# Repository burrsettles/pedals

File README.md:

# BULLFINCH EFFECTS

This repo contains work-in-progress circuit designs for DIY guitar effect pedals.

I write songs and play guitar for [delicious pastries](https://soundcloud.com/deliciouspastries/albums); as our sound has became more effects-driven, I became interested in the underlying technology of  analog effects. So I built a few boutique pedals/clones from stompbox kits and PCBs designed by others. I'm now at a point where I want to experiment with my own circuit modifications, designs, and layouts. This is a playground for that.

### Verified designs with build docs to date:

- [CYCLOPS](designs/cyclops_fuzz/) (mufflike fuzz)
- [GAIUS](designs/gaius_ringer/) (octaver / ring modulator)
- [JANUS](designs/janus_overdrive) (overdrive + distortion)
- [SIREN](designs/siren_chorus) (PT2399 chorus)

Subfolders contain files for [EAGLE](http://www.cadsoftusa.com/) schematics and two-sided circuit boards (e.g., for an [OSH Park](https://oshpark.com/) order), and maybe some documentation. The `bffx-lbr` directory contains the EAGLE library I'm using. I am not making any one-sided layouts, since I don't want to etch my own PCBs (for now). At this point, no designs are verified or even finalized. As time goes on, I will actually build and test these, and documentation will be more complete! :)

I'm naming the pedals after various mythological characters or elements.

© 2016 Burr Settles ([LICENSE](LICENSE.md))

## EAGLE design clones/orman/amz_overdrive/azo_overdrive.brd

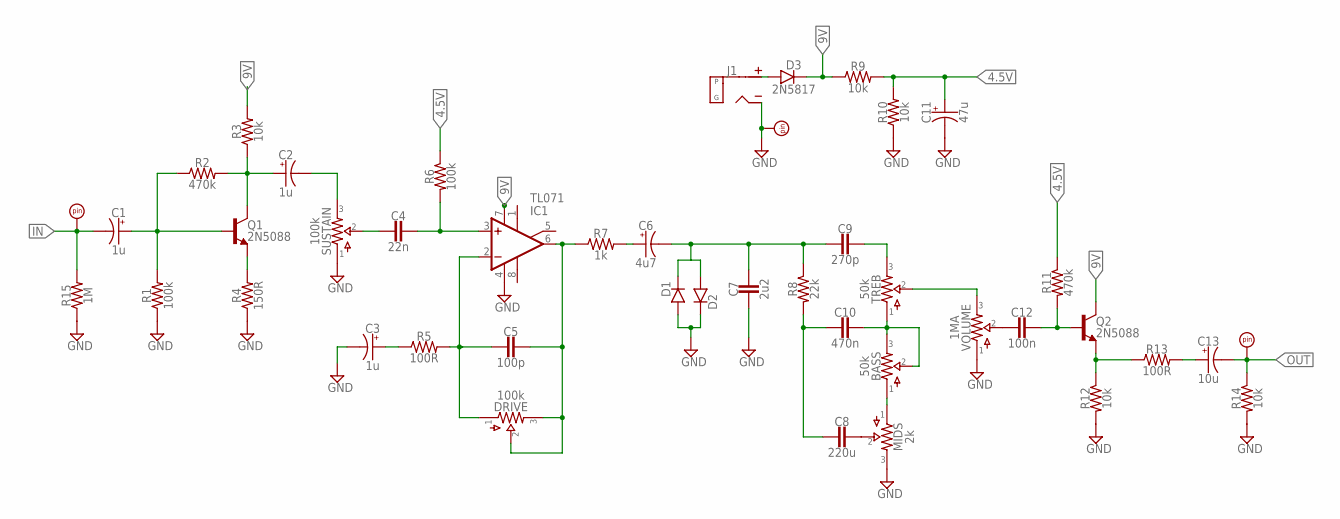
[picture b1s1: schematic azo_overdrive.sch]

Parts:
BASS: 50k; 16MM
C1, C2, C3: 1u; 050_020_1
C4: 22n; 050X030_025_2
C5: 100p; 050X030_025_2
C6: 4u7; 050_020_1
C7: 2u2; 050X030_025_2
C8: 220u; 050X030_025_2
C9: 270p; 050X030_025_2
C10: 470n; 050X030_025_2
C11: 47u; 050_020_1
C12: 100n; 050X030_025_2
C13: 10u; 050_020_1
D1, D2: DO35.2; DO35-2
D3: 2N5817; DO41-3
DRIVE: 100k; 16MM
GND: PADSQR; SQUARE
IC1: TL071; DIL08
IN: PADSQR; SQUARE
J1: DC_MONO; DC
MIDS: 2k; 16MM
OUT: PADSQR; SQUARE
Q1, Q2: 2N5088; TO92-
R1, R6: 100k; R0207/3
R2, R11: 470k; R0207/3
R3, R9, R10, R12, R14: 10k; R0207/3
R4: 150R; R0207/3
R5, R13: 100R; R0207/3
R7: 1k; R0207/3
R8: 22k; R0207/3
R15: 1M; R0207/3
SUSTAIN: 100k; 2262_TRIM
TREB: 50k; 16MM
VOLUME: 1MA; 16MM

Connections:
4.5V: C11.+, R6.1, R9.2, R10.2, R11.1
9V: D3.C, IC1.7 (V+), Q2.1 (C), R3.2, R9.1
GND: C3.-, C7.2, C11.-, D1.A, D2.C, GND.1, IC1.4 (V-), J1.S (SLEEVE), MIDS.3, R1.1, R4.1, R10.1, R12.2, R14.2, R15.1, SUSTAIN.1, VOLUME.1
IN: C1.-, IN.1, R15.2
unnamed: C1.+, Q1.2 (B), R1.2, R2.1
unnamed: C4.1, IC1.3 (+IN), R6.2
unnamed: C2.+, Q1.1 (C), R2.2, R3.1
unnamed: Q1.3 (E), R4.2
unnamed: C2.-, SUSTAIN.3
unnamed: D3.A, J1.T (TIP)
unnamed: C5.2, DRIVE.1, IC1.2 (-IN), R5.2
unnamed: C3.+, R5.1
unnamed: C4.2, SUSTAIN.2
unnamed: C6.-, C7.1, C9.2, D1.C, D2.A, R8.1
unnamed: C5.1, DRIVE.2, DRIVE.3, IC1.6 (OUT), R7.1
unnamed: C8.1, MIDS.2
unnamed: C6.+, R7.2
unnamed: C9.1, TREB.3
unnamed: C8.2, C10.2, R8.2
unnamed: BASS.2, BASS.3, C10.1, TREB.1
unnamed: BASS.1, MIDS.1
unnamed: C12.1, Q2.2 (B), R11.2
unnamed: TREB.2, VOLUME.3
unnamed: C12.2, VOLUME.2
unnamed: Q2.3 (E), R12.1, R13.1
unnamed: C13.+, R13.2
OUT: C13.-, OUT.1, R14.1

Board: 2 copper layers, 44 parts (1 on the bottom side), 27 nets, no tracks yet.

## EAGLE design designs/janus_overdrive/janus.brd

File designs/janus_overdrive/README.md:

# JANUS

**OVERDRIVE + DISTORTION**

© 2016 Burr Settles ([LICENSE](../../LICENSE.md))

### overview

JANUS is a versatile and open-ended dirt box; a mash-up of several classic 1970s distortions. The story begins with the [Dan Armstrong Blue Clipper](http://www.effectsdatabase.com/model/danarmstrong/blueclipper) (1972?), supposedly one of the first op-amp-based "smooth fuzz" effects. According to legend, someone from MXR picked one up at a NAMM convention and it was modified to create the [MXR Distortion+](https://en.wikipedia.org/wiki/MXR_Distortion_%2B) (1973). This was later was modded into the [DOD 250 Overdrive/Preamp](http://www.effectsdatabase.com/model/dod/first/250) (1976), cloned as the [Ross R-50](http://www.effectsdatabase.com/model/ross/r50) (1979), and even adapted into the [MXR MicroAmp](http://www.jimdunlop.com/product/m133-micro-amp) preamp/booster.

Since these are basically the same circuit with different component values, the same board lets you build a variant of any of them. JANUS uses a combination of values I settled on through experimentation, and adds a CLIP switch to toggle between different clipping diodes (or no diodes at all!). This makes JANUS a multi-faced, multi-purpose vintage distortion box packed into in a tiny package.

### notes

* The clipping diodes (D1-D4) are your choice. Experiment! In my build, I used a pair of 1N914s for D2-D3 (symmetrical), and a 3mm red LED coupled with a NOS germanium for D4-D5 (asymmetrical).
* If you use an on/off/on SPDT for the CLIP switch, the middle "off" position adds a third boost option. With the gain turned down and the volume up, it's a pretty transparent clean boost, but the the op-amp can be overdriven without the help of clipping diodes as you turn up the gain. But be prepared: _it is a lot louder_!
* If you don't want the CLIP switch options, you can either:
  1. jumper pin 2 to pin 1 and use D4-D5 (larger, 4-spaced diodes like germanium or Schottky), or
  2. jumper pin 2 to pin 3 and use D2-D3 (smaller, 3-spaced diodes like 1N914, 1N4148, or LEDs).
* If you want to omit the DRIVE control (as with the Blue Clipper), jumper pin 2 to 3. This is fixed at maximum gain.
* If you want to build a booster with one control (as with the MicroAmp), jumper pin 2 to 3 for the VOLUME pot, and use only the DRIVE control. (You may also want to add a 10k resistor from pin 1 to either 2 or 3 to be more faithful to that circuit). Be warned: I haven't verified this yet.

### bill of materials

I recommend building with the JANUS values, as these are the only ones I have verified.

Since I edited the circuit to my own liking and squeezed it all into a 1590a-sized board, components for some of the source circuits are omitted and you can't get a 100% faithful clone of _every_ circuit JANUS is based on. However, if you want to try a straight-up clone of one of the source effects, try the alternate component values below (column headings are links to source docs/schematics):

Part | **JANUS** | [Blue Clipper](http://tonepad.com/project.asp?id=49) | [MXR Dist+](http://tonepad.com/project.asp?id=2) | [DOD 250](https://sites.google.com/site/snmavronis/NeoClassicFX/741overdrive/research) | [Ross](http://www.home-wrecker.com/ross_distortion_tan.png) | [MicroAmp](http://www.electrosmash.com/mxr-microamp)
--- | --- | --- | --- | --- | --- | ---
C1 | **2n2** | - | 1n | - | 1n | -
C2 | **47u** | 100u | - | - | 10n | -
C3 | **10n** | 47n | 10n | 10n | 10n | 100n
C4 | **10u** | - | 1u | 10u | 1u | 1u
C5 | **47n** | 4u7 | 47n | 47n | 47n | 4u7
C6 | **4u7** | 4u7 | 1u | 4u7 | 1u | 15u
D1 | **1N5817** | - | - | - | - | -
D2-D3 | **your choice** | 1N914 (Si) | - | 1N4148 (Si) | - | -
D4-D5 | **your choice** | - | 1N270 (Ge) | - | 1N270 (Ge) | -
IC1 | **LM741** | LM741 | LM741 | LM741 | LM741 | LM741
R1 | **1M** | - | - | - | - | -
R2 | **22k** | 200k | 1M | 22k | 1M | 100k
R3 | **22k** | 240k | 1M | 22k | 1M | 100k
R4 | **4k7** | 150R | 4k7 | 4k7 | 4k7 | 2k7
R5 | **10k** | jumper | 10k | 10k | 10k | 10k
R6 | **470k** | jumper | 1M | 470k | 1M | 10M
R7 | **1M** | 150k | 1M | 1M | 1M | 56k
R8 | **10k** | 18k2 | 10k | 10k | 10k | 470R
CLIP | **SPDT** toggle | jumper 2-3 | jumper 2-1 | jumper 2-3 | jumper 2-1 | -
DRIVE | **500kC** | jumper 2-3 | 500kC | 500kC | 500kC | 500kC
VOLUME | **100kA** | 10kA | 50kA | 100kA | 50kB | jumper 2-3

Note: The Ross version supposedly used a 4558 dual op-amp. The JANUS is only laid out for single op-amp like the LM741.

### schematic

### layout

1.3" x 1.3" (1590a)

### build pics

12 June 2016

29 May 2017

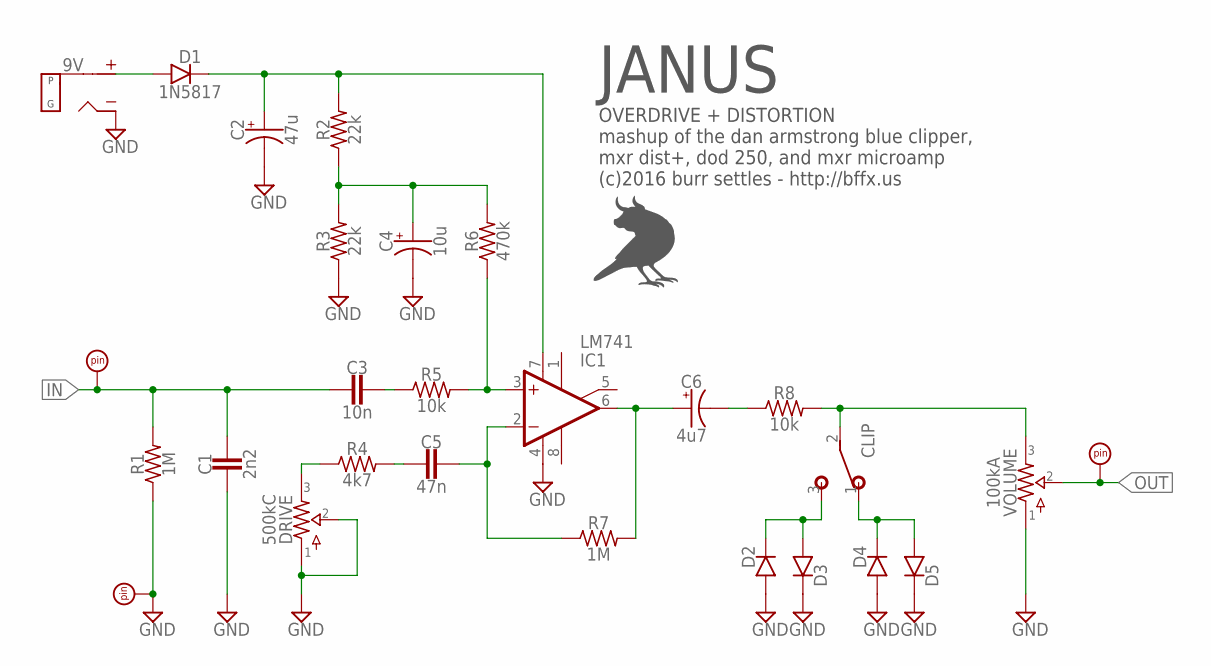
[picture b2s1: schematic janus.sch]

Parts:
9V: DC_MONO; DC
C1: 2n2; 050X030_025_2
C2: 47u; 050_020_1
C3: 10n; 050X030_025_2
C4: 10u; 050_020_1
C5: 47n; 050X030_025_2
C6: 4u7; 050_020_1
CLIP: SPDTPADS; SPDT
D1: 1N5817; DO41-3
D2, D3: DO35.2; DO35-2
D4, D5: DO35.3; DO35-3
DRIVE: 500kC; PADS_SMALL
GND: PADRND; ROUND
IC1: LM741; DIL08
IN: PADSQR; SQUARE
OUT: PADSQR; SQUARE
R1, R7: 1M; R0207/3
R2, R3: 22k; R0207/3
R4: 4k7; R0207/3
R5, R8: 10k; R0207/3
R6: 470k; R0207/3
VOLUME: 100kA; PADS_SMALL

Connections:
CLIP: CLIP.2, R8.2, VOLUME.3
GND: 9V.S (SLEEVE), C1.1, C2.-, C4.-, D2.A, D3.C, D4.A, D5.C, DRIVE.1, DRIVE.2, GND.1, IC1.4 (V-), R1.1, R3.1, VOLUME.1
IN: C1.2, C3.2, IN.1, R1.2
unnamed: C3.1, R5.1
unnamed: IC1.3 (+IN), R5.2, R6.1
unnamed: C5.1, IC1.2 (-IN), R7.1
unnamed: C5.2, R4.2
unnamed: C6.+, IC1.6 (OUT), R7.2
unnamed: C6.-, R8.1
unnamed: CLIP.3 (S), D2.C, D3.A
unnamed: C4.+, R2.1, R3.2, R6.2
unnamed: CLIP.1 (O), D4.C, D5.A
unnamed: DRIVE.3, R4.1
unnamed: 9V.T (TIP), D1.A
unnamed: C2.+, D1.C, IC1.7 (V+), R2.2
OUT: OUT.1, VOLUME.2

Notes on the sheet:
JANUS
OVERDRIVE + DISTORTION mashup of the dan armstrong blue clipper, mxr dist+, dod 250, and mxr microamp (c)2016 burr settles - http://bffx.us

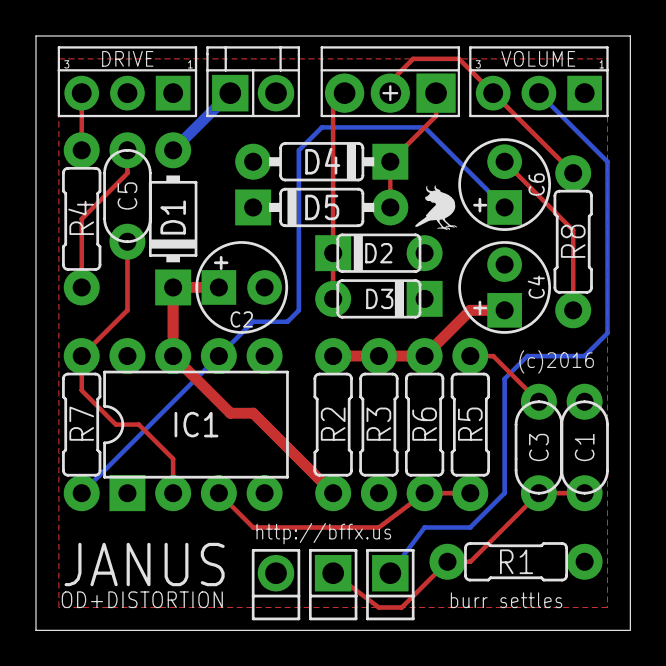
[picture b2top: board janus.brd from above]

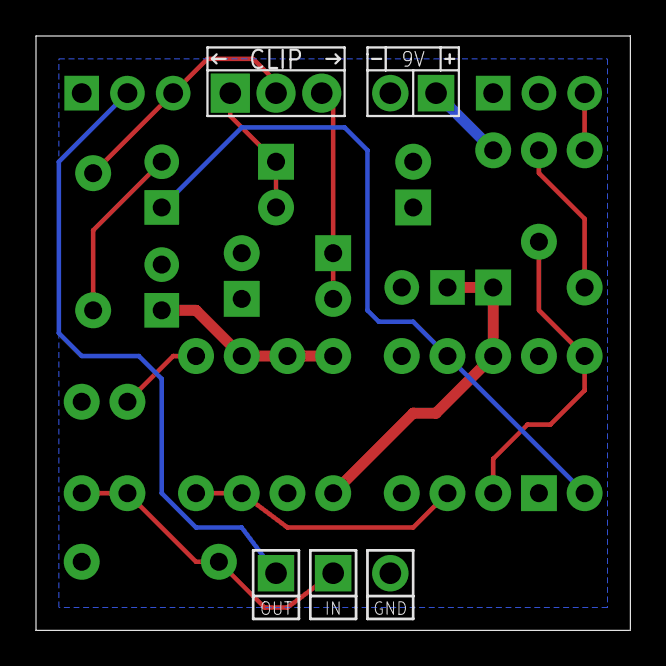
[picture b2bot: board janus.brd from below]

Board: 2 copper layers, 33.0 x 33.0 mm, 28 parts (2 on the bottom side), 16 nets.

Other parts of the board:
U$1: BF0100

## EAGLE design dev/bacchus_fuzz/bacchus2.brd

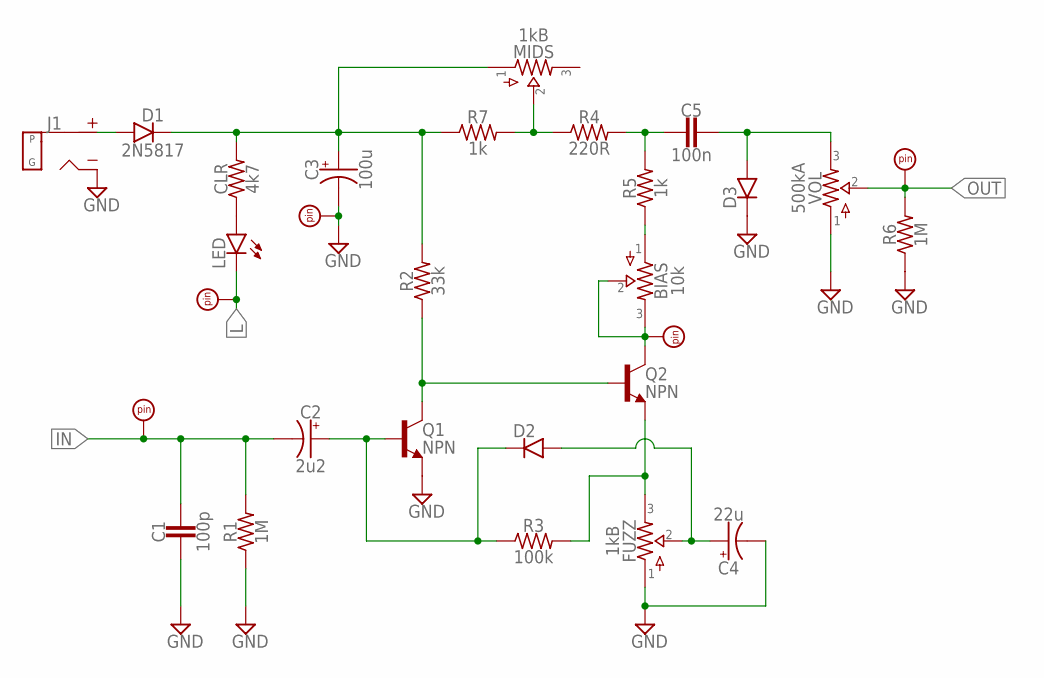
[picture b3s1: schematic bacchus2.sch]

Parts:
BIAS: 10k; 2262_TRIM
C1: 100p; 050X030_025_2
C2: 2u2; 050_020_1
C3: 100u; 050_020_1
C4: 22u; 050_020_1
C5: 100n; 050X030_025_2
CLR: 4k7; R0207/3
D1: 2N5817; DO41-3
D2, D3: DO35.2; DO35-2
FUZZ: 1kB; 9MM_W/MOUNTS
GND: PADRND; ROUND
IN: PADSQR; SQUARE
J1: DC_MONO; DC
L: PADRND; ROUND
LED: LEDB; 3MM_B
MIDS: 1kB; 9MM_W/MOUNTS
OUT: PADSQR; SQUARE
Q1, Q2: NPN; TO5
R1, R6: 1M; R0207/3
R2: 33k; R0207/3
R3: 100k; R0207/3
R4: 220R; R0207/3
R5, R7: 1k; R0207/3
TP: PADSQR; SQUARE
VOL: 500kA; 9MM_W/MOUNTS

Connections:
GND: C1.2, C3.-, C4.-, D3.C, FUZZ.P$1 (1), GND.1, J1.S (SLEEVE), Q1.1 (E), R1.1, R6.1, VOL.P$1 (1)
IN: C1.1, C2.-, IN.1, R1.2
L: L.1, LED.K (C)
unnamed: C5.1, D3.A, VOL.P$3 (3)
unnamed: C2.+, D2.C, Q1.2 (B), R3.1
unnamed: Q1.3 (C), Q2.2 (B), R2.1
unnamed: D1.A, J1.T (TIP)
unnamed: C3.+, CLR.2, D1.C, MIDS.P$1 (1), R2.2, R7.1
unnamed: MIDS.P$2 (2), R4.1, R7.2
unnamed: CLR.1, LED.A
unnamed: C5.2, R4.2, R5.2
unnamed: BIAS.1, R5.1
unnamed: BIAS.2, BIAS.3, Q2.3 (C), TP.1
unnamed: FUZZ.P$3 (3), Q2.1 (E), R3.2
unnamed: C4.+, D2.A, FUZZ.P$2 (2)
OUT: OUT.1, R6.2, VOL.P$2 (2)

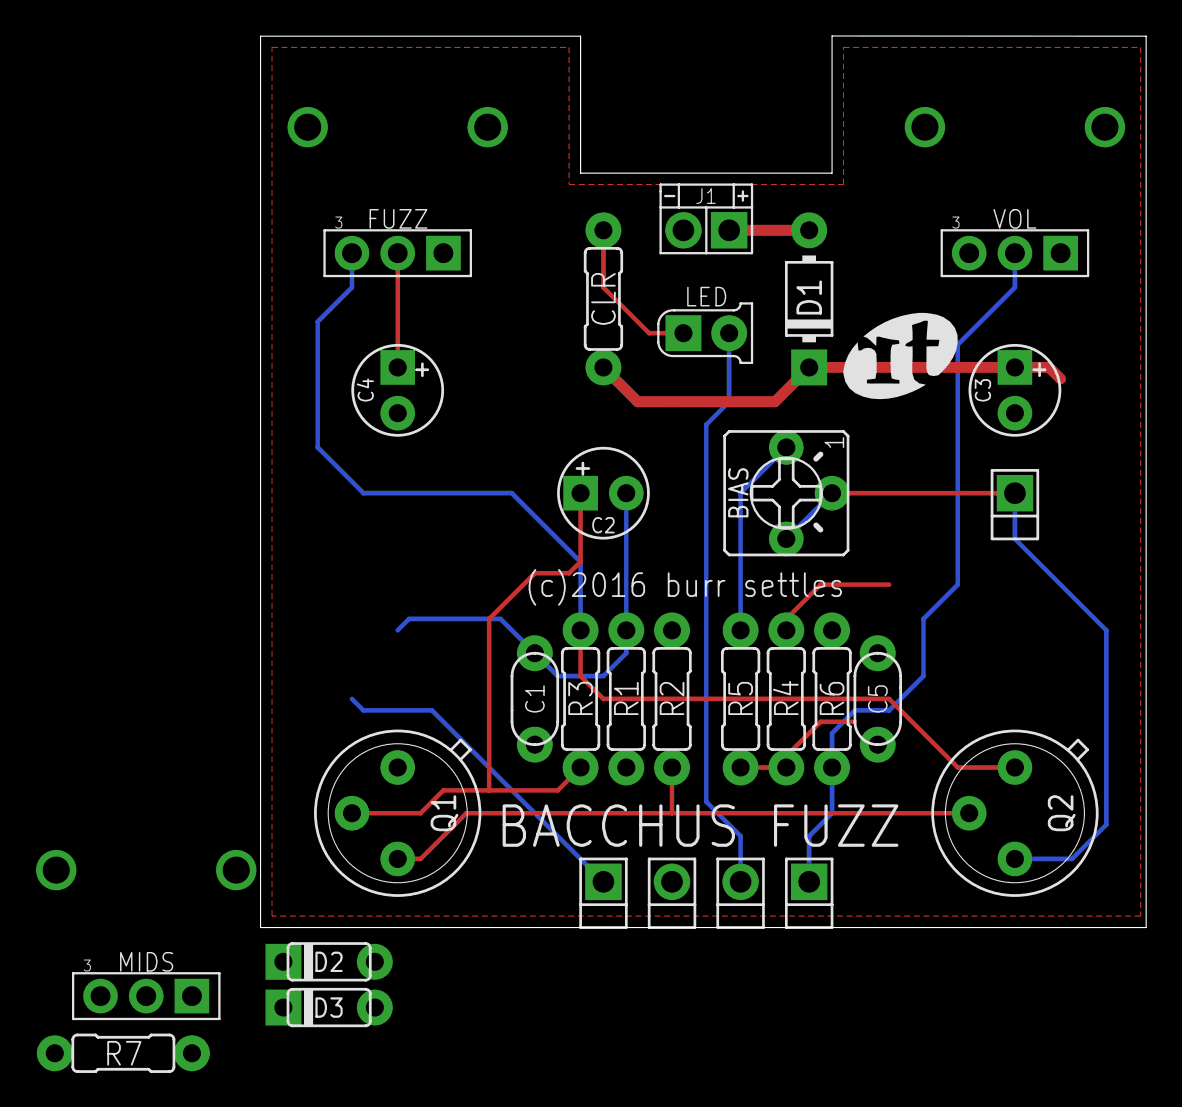
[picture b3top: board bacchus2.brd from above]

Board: 2 copper layers, 49.2 x 49.5 mm, 30 parts (0 on the bottom side), 16 nets.

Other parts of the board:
U$4: RT0250

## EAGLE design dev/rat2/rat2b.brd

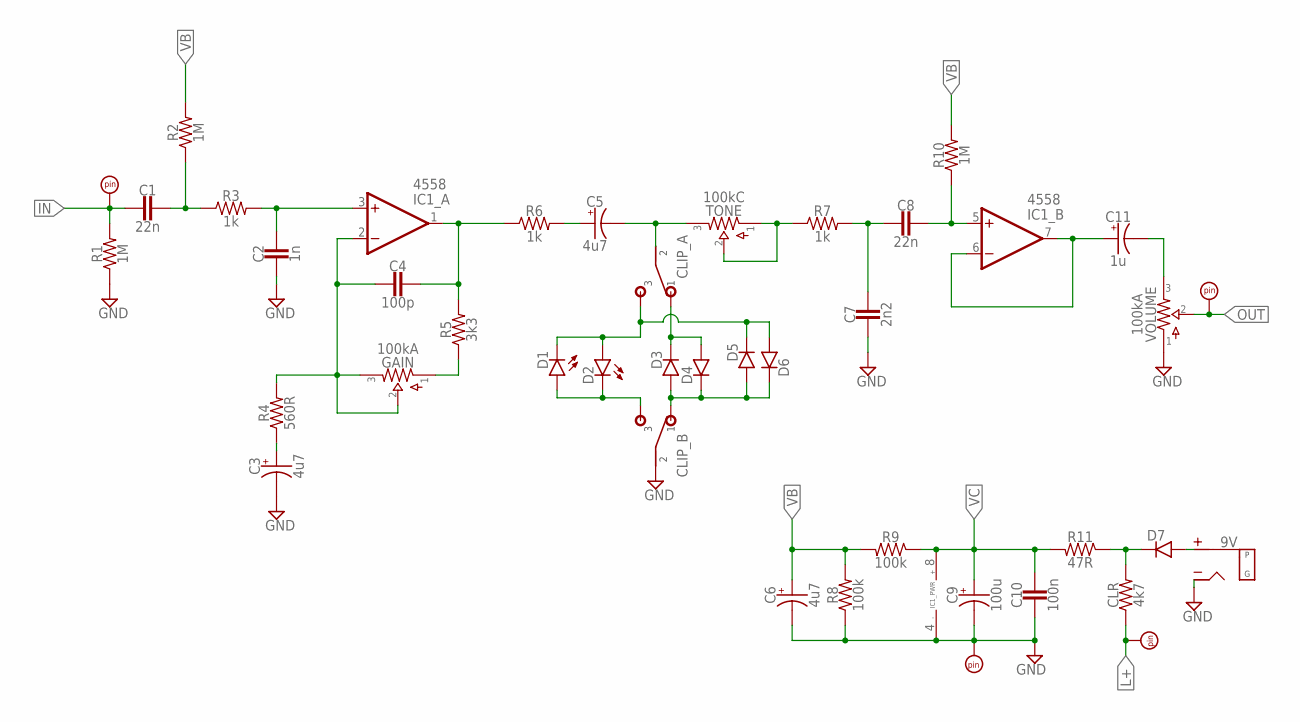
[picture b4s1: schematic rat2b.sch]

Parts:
9V: DC_MONO; DC
C1, C8: 22n; 050X030_025_2
C2: 1n; 050X030_025_2
C3, C5, C6: 4u7; 050_020_1
C4: 100p; 050X030_025_2
C7: 2n2; 050X030_025_2
C9: 100u; 050_020_1
C10: 100n; 050X030_025_2
C11: 1u; 050_020_1
CLIP: DPDTPCB; DPDT2_PCB
CLR: 4k7; R0207/3
D1, D2: LEDB; 3MM_B
D3, D4: DO35.3; DO35-3
D5, D6: DO35.2; DO35-2
D7: DO41.3; DO41-3
GAIN: 100kA; 16MM
GND: PADRND; ROUND
IC1: 4558; DIL08
IN: PADSQR; SQUARE
LED: PADSQR; SQUARE
OUT: PADSQR; SQUARE
R1, R2, R10: 1M; R0207/3
R3, R6, R7: 1k; R0207/3
R4: 560R; R0207/3
R5: 3k3; R0207/3
R8, R9: 100k; R0207/3
R11: 47R; R0207/3
TONE: 100kC; 16MM
VOLUME: 100kA; 16MM

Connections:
GND: 9V.S (SLEEVE), C2.2, C3.-, C6.-, C7.2, C9.-, C10.2, CLIP.B2 (2), GND.1, IC1.4 (V-), R1.1, R8.1, VOLUME.1
IN: C1.2, IN.1, R1.2
L+: CLR.1, CLR.2, D7.C, LED.1, R11.1
unnamed: C1.1, R2.1, R3.1
unnamed: C2.1, IC1.3 (+IN), R3.2
unnamed: GAIN.1, R5.1
unnamed: C4.1, IC1.1 (OUT), R5.2, R6.1
unnamed: C5.+, R6.2
unnamed: C5.-, CLIP.A2 (2), TONE.3
unnamed: R7.1, TONE.1, TONE.2
unnamed: C7.1, C8.2, R7.2
unnamed: C8.1, IC1.5 (+IN), R10.1
unnamed: CLIP.A1 (1), D3.C, D4.A
unnamed: C11.-, VOLUME.3
unnamed: CLIP.B1 (1), D3.A, D4.C, D5.A, D6.C
unnamed: C4.2, GAIN.2, GAIN.3, IC1.2 (-IN), R4.2
unnamed: C11.+, IC1.6 (-IN), IC1.7 (OUT)
unnamed: C3.+, R4.1
unnamed: 9V.T (TIP), D7.A
unnamed: CLIP.A3 (3), D1.K (C), D2.A, D5.C, D6.A
unnamed: CLIP.B3 (3), D1.A, D2.K (C)
OUT: OUT.1, VOLUME.2
VB: C6.+, R2.2, R8.2, R9.2, R10.2
VC: C9.+, C10.1, IC1.8 (V+), R9.1, R11.2

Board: 2 copper layers, 43 parts (0 on the bottom side), 24 nets, no tracks yet.

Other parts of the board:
U$1: BF0200
U$2: 1590B
U$3: DC_TOP

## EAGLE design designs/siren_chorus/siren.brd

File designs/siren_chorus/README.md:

# SIREN

**PT2399 CHORUS**

© 2016 Burr Settles ([LICENSE](../../LICENSE.md))

### overview

SIREN is a tiny chorus pedal based on the [MBP Glam](http://madbeanpedals.com/projects/1590G/Glam.pdf), which in turn was inspired by the [Little Angel](http://www.diystompboxes.com/smfforum/index.php?topic=86297.0) and several other attempts to use a modulated PT2399 delay chip to create a chorus effect. The end result doesn't feel like a "true" chorus — in fact it's a bit like a cross between a slapback delay and a chorus. But and interesting effect nonetheless.

I redesigned the circuit to fit in a 1590a enclosure, with a few other tweaks (optional trimpot for depth control, pulsing rate indicator LED, etc.). Here are the results!

### notes

* The board was designed for 1/8W resistors (2-hole spacing)
* The `DEPTH` pot is laid out for an internal trimpot ("set it and forget it"), as I used it in my build below. However, you can easily wire it up as an off-board depth control if you wish.
* If you want the indicator LED to pulse with the LFO/rate, just connect the LED anode via a current-limiting resistor to the `L+` pad (instead of directly to the 9V+ power source). Connect the cathode to the footswitch as normal.

### bill of materials

Qty | Parts | Value
--- | ----- | -----
4 | C1, C5, C11, C20 | 10n
1 | C2 | 47u
6 | C3, C9, C14, C15, C17, C18 | 100n
2 | C4, C12 | 10u
1 | C6 | 22n
2 | C7, C16 | 220n
1 | C8 | 10u
1 | C10 | 2n2
1 | C13 | 100p
1 | C19 | 4u7
2 | R1, R2 | 100k
2 | R3, R4 | 220k
2 | R5, R7 | 1M
1 | R6 | 15k
5 | R8, R11, R13, R15, R19 | 10k
3 | R10, R12, R14 | 18k
1 | R16 | 2k
1 | R17 | 12k
1 | R18 | 4k7
1 | D1 | 1N4817
1 | IC1 | NE5532
1 | IC2 | PT2399TH
1 | Q1 | 2N5457
1 | REG1 | LM78L05
1 | POT: BIAS | 50k (trim)
1 | POT: DEPTH | 10kB
1 | POT: RATE | 100kC

### schematic

### layout

1.3" x 2.1" (1590a)

### build pic

29 May 2017

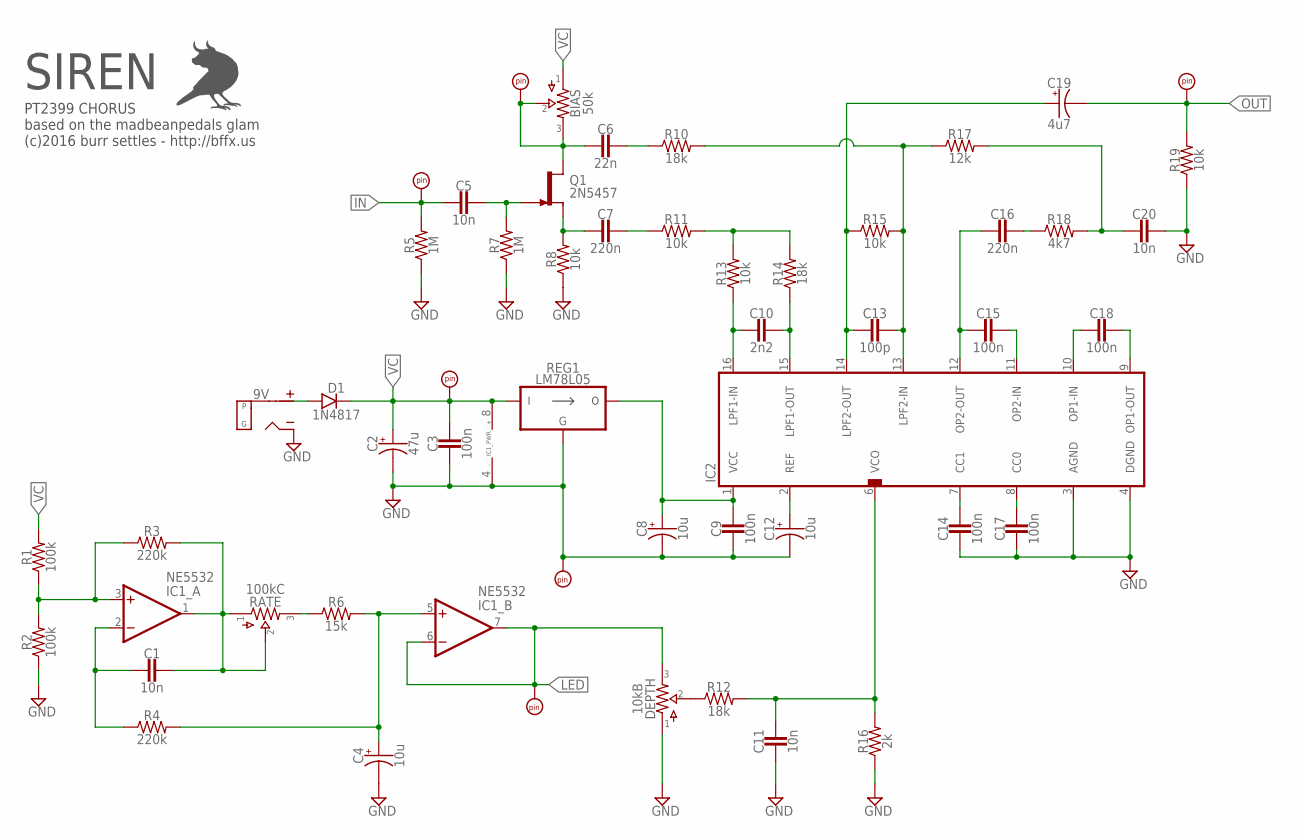
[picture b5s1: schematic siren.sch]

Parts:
9V: DC_MONO; DC
BIAS: 50k; 2262_TRIM
C1, C5, C11, C20: 10n; 050X030_025_2
C2: 47u; 050_020_1
C3, C9, C14, C15, C17, C18: 100n; 050X030_025_2
C4, C12: 10u; 050_020_1
C6: 22n; 050X030_025_2
C7, C16: 220n; 050X030_025_2
C8: 10u; 050_020
C10: 2n2; 050X030_025_2
C13: 100p; 050X030_025_2
C19: 4u7; 050_020_1
D1: 1N4817; DO41-3
DEPTH: 10kB; 2262_TRIM
GND: PADRND; ROUND
IC1: NE5532; DIL08
IC2: PT2399TH; DIL16
IN: PADSQR; SQUARE
L+: PADSQR; SQUARE
OUT: PADSQR; SQUARE
PAD1, PAD2: PAD; UNLABELED
Q1: 2N5457; TO92-
R1, R2: 100k; R0207/2V
R3, R4: 220k; R0207/2V
R5, R7: 1M; R0207/2V
R6: 15k; R0207/2V
R8, R11, R13, R15, R19: 10k; R0207/2V
R10, R12, R14: 18k; R0207/2V
R16: 2k; R0207/2V
R17: 12k; R0207/2V
R18: 4k7; R0207/2V
RATE: 100kC; PADS_SMALL
REG1: LM78L05; TO92-

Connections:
+9V: 9V.T (TIP), D1.A
GND: 9V.S (SLEEVE), C2.-, C3.2, C4.-, C8.-, C9.2, C11.2, C12.-, C14.2, C17.2, C20.1, DEPTH.1, GND.1, IC1.4 (V-), IC2.3 (AGND), IC2.4 (DGND), R2.1, R5.1, R7.1, R8.1, R16.1, R19.1, REG1.2 (GND)
IN: C5.2, IN.1, R5.2
LED: DEPTH.3, IC1.6 (-IN), IC1.7 (OUT), L+.1
unnamed: C13.1, IC2.13 (LPF2-IN), R10.2, R15.2, R17.1
unnamed: C8.+, C9.1, IC2.1 (VCC), REG1.3 (VO)
unnamed: C10.2, IC2.16 (LPF1-IN), R13.1
unnamed: C10.1, IC2.15 (LPF1-OUT), R14.1
unnamed: C20.2, R17.2, R18.2
unnamed: C12.+, IC2.2 (REF)
unnamed: C14.1, IC2.7 (CC1)
unnamed: C17.1, IC2.8 (CC0)
unnamed: C15.1, IC2.11 (OP2-IN)
unnamed: C18.2, IC2.10 (OP1-IN)
unnamed: C18.1, IC2.9 (OP1-OUT)
unnamed: C13.2, C19.+, IC2.14 (LPF2-OUT), R15.1
unnamed: R11.2, R13.2, R14.2
unnamed: C7.1, R11.1
unnamed: C7.2, Q1.2 (S), R8.2
unnamed: C6.1, R10.1
unnamed: BIAS.2, BIAS.3, C6.2, PAD2.P$1, Q1.3 (D)
unnamed: C5.1, Q1.1 (G), R7.2
unnamed: IC1.3 (+IN), R1.1, R2.2, R3.1
unnamed: C15.2, C16.2, IC2.12 (OP2-OUT)
unnamed: C16.1, R18.1
unnamed: C1.1, IC1.1 (OUT), R3.2, RATE.1, RATE.2
unnamed: C1.2, IC1.2 (-IN), R4.1
unnamed: DEPTH.2, R12.1
unnamed: R6.1, RATE.3
unnamed: C4.+, IC1.5 (+IN), R4.2, R6.2
unnamed: C11.1, IC2.6 (VCO), R12.2, R16.2
OUT: C19.-, OUT.1, R19.2
VC: BIAS.1, C2.+, C3.1, D1.C, IC1.8 (V+), PAD1.P$1, R1.2, REG1.1 (VI)

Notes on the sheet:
PT2399 CHORUS based on the madbeanpedals glam (c)2016 burr settles - http://bffx.us
SIREN

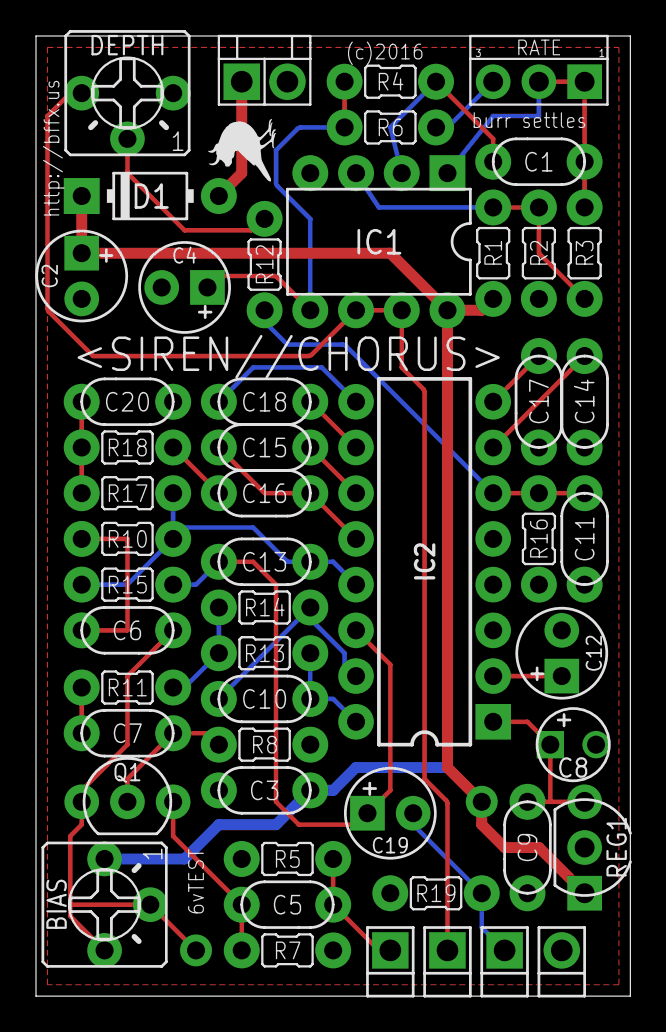
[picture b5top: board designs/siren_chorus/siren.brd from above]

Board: 2 copper layers, 33.0 x 53.3 mm, 54 parts (1 on the bottom side), 33 nets.

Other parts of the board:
U$1: BF0150

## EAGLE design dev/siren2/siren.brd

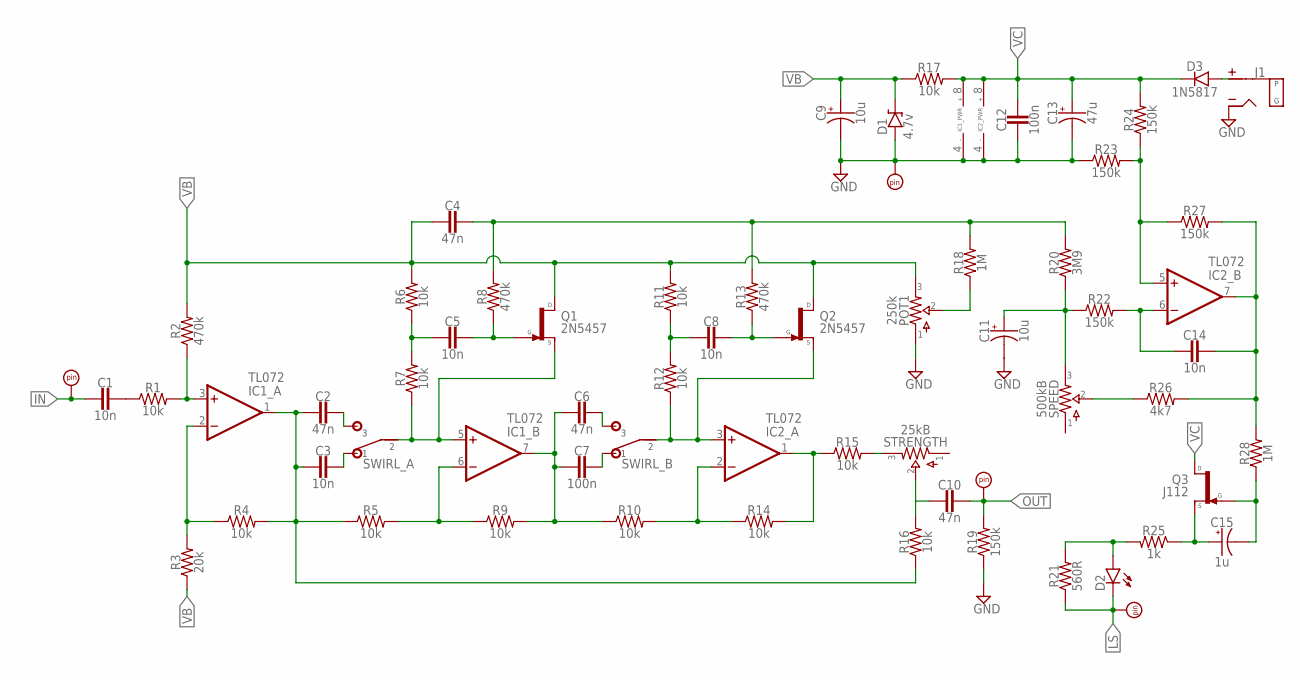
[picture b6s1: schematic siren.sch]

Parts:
C1, C3, C5, C8, C14: 10n; 050X030_025_2
C2, C4, C6, C10: 47n; 050X030_025_2
C7, C12: 100n; 050X030_025_2
C9, C11: 10u; 050_020_1
C13: 47u; 050_020_1
C15: 1u; 050_020_1
D1: 4.7v; DO41-2
D2: LEDB; 3MM_B
D3: 1N5817; DO41-3
IC1, IC2: TL072; DIL08
J1: DC_MONO; DC
PAD1, PAD3, PAD4: PADSQR; SQUARE
PAD2: PADRND; ROUND
POT1: 250k; 2262_TRIM
Q1, Q2: 2N5457; TO92-
Q3: J112; TO92-
R1, R4, R5, R6, R7, R9, R10, R11, R12, R14, R15, R16, R17: 10k; R0207/3
R2, R8, R13: 470k; R0207/3
R3: 20k; R0207/3
R18, R28: 1M; R0207/3
R19, R22, R23, R24, R27: 150k; R0207/3
R20: 3M9; R0207/3
R21: 560R; R0207/3
R25: 1k; R0207/3
R26: 4k7; R0207/3
SPEED: 500kB; 16MM
STRENGTH: 25kB; 16MM
SWIRL: DPDTPADS; DPDT_PADS

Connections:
GND: C9.-, C11.-, C12.2, C13.-, D1.A, IC1.4 (V-), IC2.4 (V-), J1.S (SLEEVE), PAD2.1, POT1.1, R19.1, R23.1
IN: C1.2, PAD1.1
LS: D2.K (C), PAD4.1, R21.1
unnamed: C1.1, R1.1
unnamed: IC1.3 (+IN), R1.2, R2.1
unnamed: C2.2, C3.2, IC1.1 (OUT), R4.2, R5.1, R16.1
unnamed: IC1.5 (+IN), Q1.2 (S), R7.1, SWIRL.P$2 (2)
unnamed: IC2.1 (OUT), R14.2, R15.1
unnamed: C10.2, R16.2, STRENGTH.2
unnamed: IC1.2 (-IN), R3.2, R4.1
unnamed: POT1.2, R18.1
unnamed: R26.1, SPEED.2
unnamed: C5.2, R6.1, R7.2
unnamed: C5.1, Q1.1 (G), R8.1
unnamed: C11.+, R20.1, R22.1, SPEED.3
unnamed: C4.1, R8.2, R13.2, R18.2, R20.2
unnamed: C14.2, IC2.6 (-IN), R22.2
unnamed: IC1.6 (-IN), R5.2, R9.1
unnamed: C14.1, IC2.7 (OUT), R26.2, R27.2, R28.2
unnamed: IC2.2 (-IN), R10.2, R14.1
unnamed: C6.2, C7.2, R9.2, R10.1
unnamed: C15.-, Q3.1 (G), R28.1
unnamed: C8.2, R11.1, R12.2
unnamed: C8.1, Q2.1 (G), R13.1
unnamed: IC2.5 (+IN), R23.2, R24.1, R27.1
unnamed: D3.A, J1.T (TIP)
unnamed: R15.2, STRENGTH.3
unnamed: C2.1, SWIRL.P$3 (3)
unnamed: C3.1, SWIRL.P$1 (1)
unnamed: C15.+, Q3.2 (S), R25.1
unnamed: IC2.3 (+IN), Q2.2 (S), R12.1, SWIRL.P$5 (2)
unnamed: C6.1, SWIRL.P$6 (3)
unnamed: C7.1, SWIRL.P$4 (1)
unnamed: D2.A, R21.2, R25.2
OUT: C10.1, PAD3.1, R19.2
VB: C4.2, C9.+, D1.C, POT1.3, Q1.3 (D), Q2.3 (D), R2.2, R3.1, R6.2, R11.2, R17.1
VC: C12.1, C13.+, D3.C, IC1.8 (V+), IC2.8 (V+), Q3.3 (D), R17.2, R24.2

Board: 2 copper layers, 68 parts (0 on the bottom side), 37 nets, no tracks yet.

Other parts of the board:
U$1: 1590B_GUIDE
U$2: 1590B
U$3: DC_TOP
U$4, U$5: LED
U$6, U$7: MONO_ENCLOSED
U$8: 3PDT

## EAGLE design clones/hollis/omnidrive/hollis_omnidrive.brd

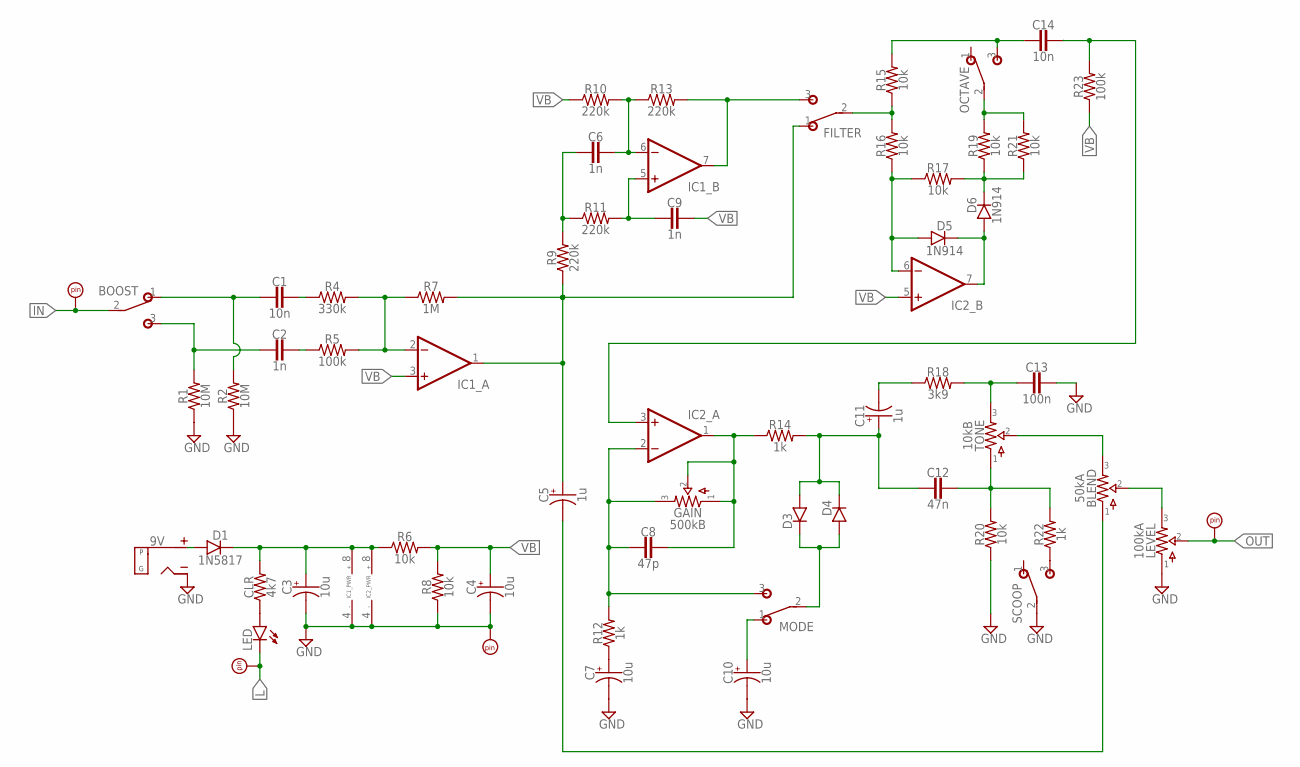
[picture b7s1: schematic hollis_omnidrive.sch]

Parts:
9V: DC_MONO; DC
BLEND: 50kA; 16MM
BOOST: SPDT; M9040P
C1, C14: 10n; 050X030_025_2
C2, C6, C9: 1n; 050X030_025_2
C3, C4, C7, C10: 10u; 050_020_1
C5, C11: 1u; 050_020_1
C8: 47p; 050X030_025_2
C12: 47n; 050X030_025_2
C13: 100n; 050X030_025_2
CLR: 4k7; R0207/3
D1: 1N5817; DO41-3
D3, D4: DO35.3; DO35-3
D5, D6: 1N914; DO35-2
FILTER: SPDT; M9040P
GAIN: 500kB; 16MM
GND: PADRND; ROUND
IC1, IC2: DUALTH; DIL08
IN: PADSQR; SQUARE
L: PADRND; ROUND
LED: LEDB; 3MM_B
LEVEL: 100kA; 16MM
MODE: SPDT; M9040P
OCTAVE: SPDT; M9040P
OUT: PADSQR; SQUARE
R1, R2: 10M; R0207/3
R4: 330k; R0207/3
R5, R23: 100k; R0207/3
R6, R8, R15, R16, R17, R19, R20, R21: 10k; R0207/3
R7: 1M; R0207/3
R9, R10, R11, R13: 220k; R0207/3
R12, R14, R22: 1k; R0207/3
R18: 3k9; R0207/3
SCOOP: SPDT; M9040P
TONE: 10kB; 16MM

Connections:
GND: 9V.S (SLEEVE), C3.-, C4.-, C7.-, C10.-, C13.1, GND.1, IC1.4 (V-), IC2.4 (V-), LEVEL.1, R1.1, R2.1, R8.1, R20.1, SCOOP.2
IN: BOOST.2, IN.1
L: L.1, LED.K (C)
MODE: D3.C, D4.A, MODE.2
unnamed: 9V.T (TIP), D1.A
unnamed: C5.+, FILTER.1 (O), IC1.1 (OUT), R7.2, R9.1
unnamed: BOOST.1 (O), C1.2, R2.2
unnamed: C1.1, R4.1
unnamed: C2.1, R5.1
unnamed: IC1.2 (-IN), R4.2, R5.2, R7.1
unnamed: C6.2, R9.2, R11.1
unnamed: BOOST.3 (S), C2.2, R1.2
unnamed: FILTER.2, R15.1, R16.2
unnamed: C6.1, IC1.6 (-IN), R10.2, R13.1
unnamed: FILTER.3 (S), IC1.7 (OUT), R13.2
unnamed: D5.A, IC2.6 (-IN), R16.1, R17.1
unnamed: C9.1, IC1.5 (+IN), R11.2
unnamed: C14.2, OCTAVE.3 (S), R15.2
unnamed: C3.+, CLR.2, D1.C, IC1.8 (V+), IC2.8 (V+), R6.1
unnamed: D5.C, D6.A, IC2.7 (OUT)
unnamed: D6.C, R17.2, R19.1, R21.1
unnamed: C14.1, IC2.3 (+IN), R23.2
unnamed: C8.2, GAIN.3, IC2.2 (-IN), MODE.3 (S), R12.2
unnamed: C8.1, GAIN.1, GAIN.2, IC2.1 (OUT), R14.1
unnamed: C7.+, R12.1
unnamed: BLEND.1, C5.-
unnamed: C10.+, MODE.1 (O)
unnamed: C11.-, R18.1
unnamed: C13.2, R18.2, TONE.3
unnamed: C12.1, R20.2, R22.2, TONE.1
unnamed: BLEND.3, TONE.2
unnamed: CLR.1, LED.A
unnamed: R22.1, SCOOP.3 (S)
unnamed: BLEND.2, LEVEL.3
unnamed: C11.+, C12.2, D3.A, D4.C, R14.2
OCTAVE: OCTAVE.2, R19.2, R21.2
OUT: LEVEL.2, OUT.1
VB: C4.+, C9.2, IC1.3 (+IN), IC2.5 (+IN), R6.2, R8.2, R10.1, R23.1

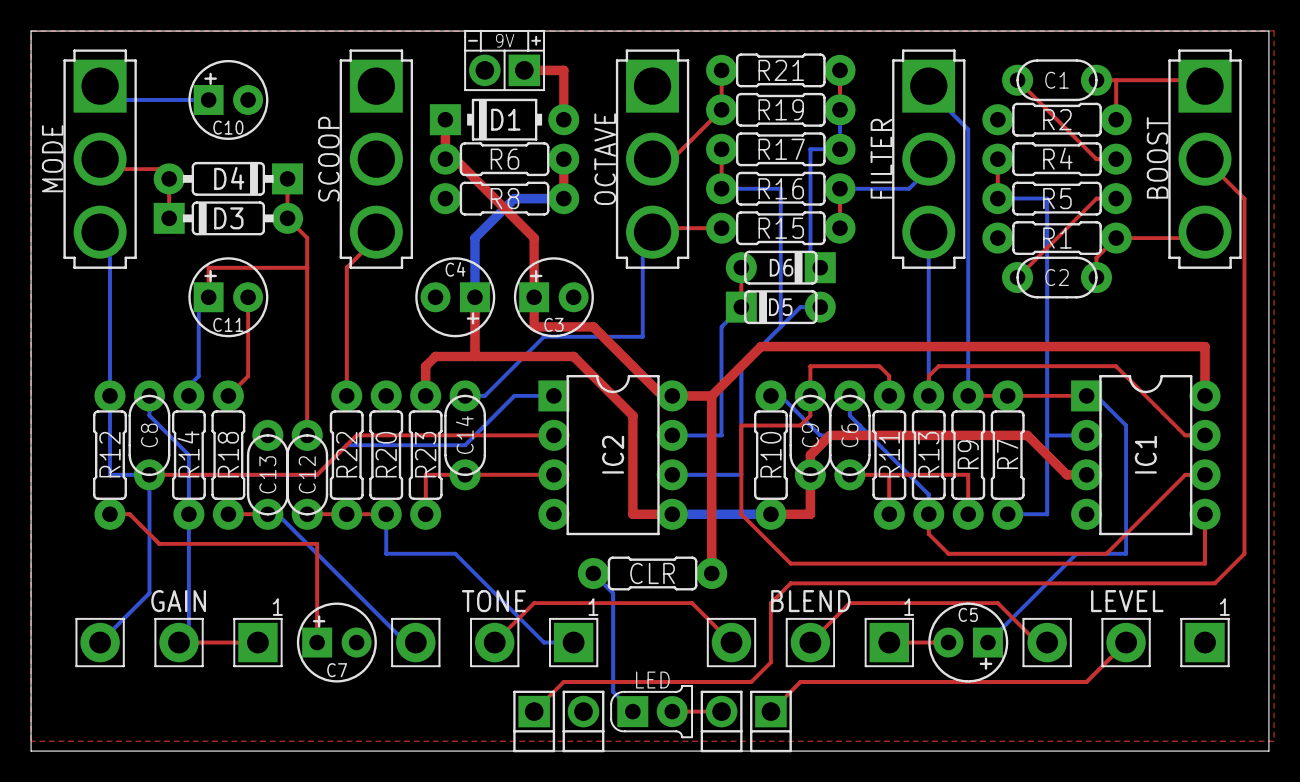
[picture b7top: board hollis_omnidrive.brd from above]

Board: 2 copper layers, 79.7 x 46.3 mm, 59 parts (0 on the bottom side), 38 nets.

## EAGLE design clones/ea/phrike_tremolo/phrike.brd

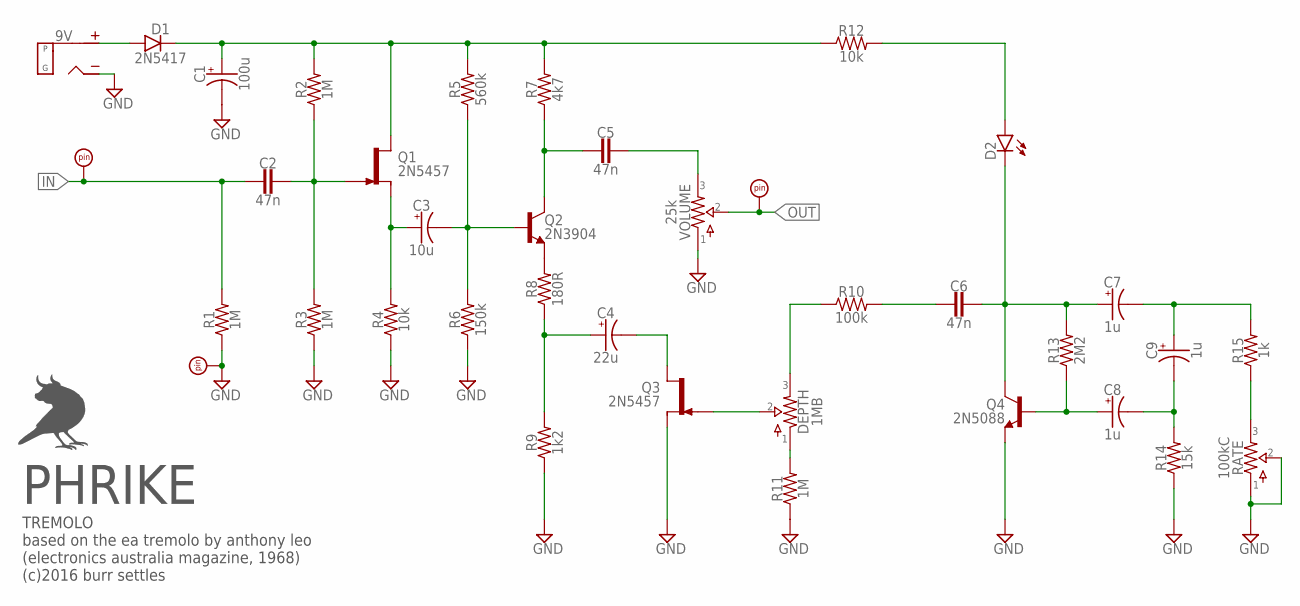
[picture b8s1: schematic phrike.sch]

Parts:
9V: DC_MONO; DC
C1: 100u; 063_025
C2, C5, C6: 47n; 050X030_025_2
C3: 10u; 050_020_1
C4: 22u; 050_020_1
C7, C8, C9: 1u; 050_020_1
D1: 2N5417; DO41-3
D2: LEDA; 3MM_A
DEPTH: 1MB; 2262_TRIM
GND: PADRND; ROUND
IN: PADSQR; SQUARE
OUT: PADSQR; SQUARE
Q1, Q3: 2N5457; TO92-
Q2: 2N3904; TO92-L2
Q4: 2N5088; TO92-
R1, R2, R3, R11: 1M; R0207/3
R4, R12: 10k; R0207/3
R5: 560k; R0207/3
R6: 150k; R0207/3
R7: 4k7; R0207/3
R8: 180R; R0207/3
R9: 1k2; R0207/3
R10: 100k; R0207/3
R13: 2M2; R0207/3
R14: 15k; R0207/3
R15: 1k; R0207/3
RATE: 100kC; PADS_SMALL
VOLUME: 25k; 2262_TRIM

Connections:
+9V: 9V.T (TIP), D1.A
GND: 9V.S (SLEEVE), C1.-, GND.1, Q3.2 (S), Q4.3 (E), R1.1, R3.1, R4.1, R6.1, R9.1, R11.1, R14.1, RATE.1, RATE.2, VOLUME.1
IN: C2.2, IN.1, R1.2
unnamed: C2.1, Q1.1 (G), R2.1, R3.2
unnamed: C3.+, Q1.2 (S), R4.2
unnamed: C3.-, Q2.2 (B), R5.1, R6.2
unnamed: C5.2, Q2.1 (C), R7.1
unnamed: Q2.3 (E), R8.2
unnamed: C5.1, VOLUME.3
unnamed: C1.+, D1.C, Q1.3 (D), R2.2, R5.2, R7.2, R12.1
unnamed: C4.+, R8.1, R9.2
unnamed: C4.-, Q3.3 (D)
unnamed: DEPTH.2, Q3.1 (G)
unnamed: DEPTH.3, R10.1
unnamed: C6.2, R10.2
unnamed: C6.1, C7.+, D2.K (C), Q4.1 (C), R13.2
unnamed: C8.+, Q4.2 (B), R13.1
unnamed: C7.-, C9.+, R15.2
unnamed: C8.-, C9.-, R14.2
unnamed: DEPTH.1, R11.2
unnamed: R15.1, RATE.3
unnamed: D2.A, R12.2
OUT: OUT.1, VOLUME.2

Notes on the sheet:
PHRIKE
TREMOLO based on the ea tremolo by anthony leo (electronics australia magazine, 1968) (c)2016 burr settles

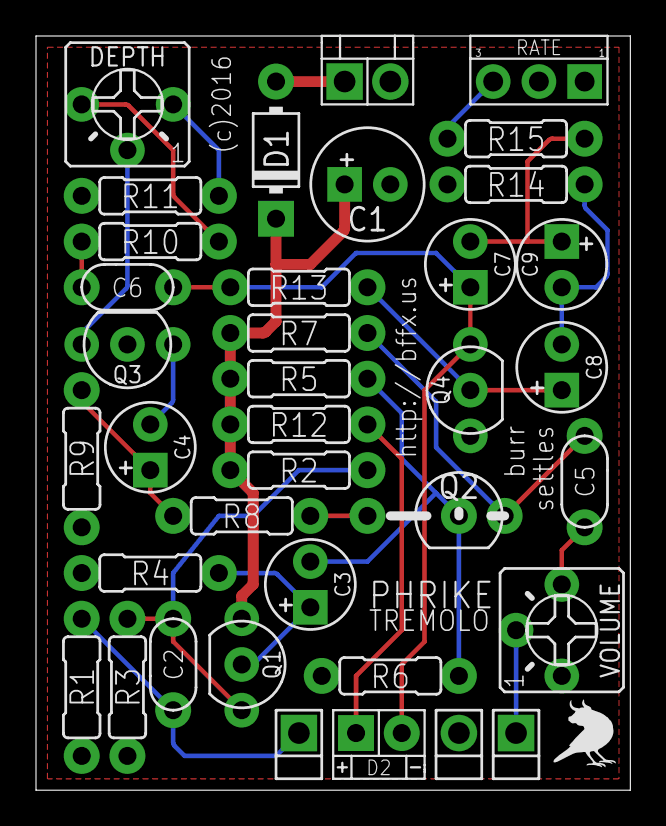
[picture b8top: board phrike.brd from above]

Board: 2 copper layers, 33.0 x 41.9 mm, 38 parts (1 on the bottom side), 23 nets.

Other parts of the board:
U$1: BF0150

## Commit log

2016-04-04 first batch of 1590a and 1590b pedals
2016-04-10 updated Gaius Ringer & Janus Drive, added Chimera Chorus
2016-04-11 updates to a few small pedals
2016-04-13 added phaser schematic; minor board tweaks
2016-04-14 formatting updates
2016-04-20 add beginnings of tremolo; minor copy tweaks to other schems
2016-04-24 add EAGLE library, update 1590a chorus and tremolo, other minor edits
2016-04-24 reorganize directory structure
2016-04-25 finished chorus and tremolo baords; other tweaks & polish
2016-04-25 prettified schematics a bit
2016-05-01 added RT logo; converted some pots trimmers
2016-05-02 updates to cerberus and cyclops
2016-05-02 little edits & cleanup
2016-05-10 convert bitmap logos to polygons
2016-05-10 .brd logo layer correction
2016-05-15 added bacchus 1590b fuzz (npn fulltone 69)
2016-05-16 added SQUONK (envelope filter)
2016-05-30 add GAIUS documentation
2016-05-30 add GAIUS readme
2016-05-30 update GAIUS readme
2016-05-30 add CYCLOPS documentation
2016-05-30 add JANUS documentation
2016-05-30 add CC BY-MC-SA license
2016-05-30 update documenation
2016-05-30 add wiring diagram
2016-05-30 fix wiring diagram
2016-05-30 update wiring diagram
2016-06-15 updated JANUS docs
2016-06-15 JANUS readme updates
2016-06-22 added build pics for CYCLOPS, GAIUS, and JANUS
2016-06-23 add a couple utility projects
2016-06-26 new logo, added TITAN 1590b fuzz
2016-12-11 updated library + logos
2016-12-11 updated schemic + layout images
2016-12-20 modify 3pdt lbr
2016-12-20 3pdt true bypass utility board
2016-12-20 correct bffx logo layer
2017-05-30 add SIREN build doc
2017-06-03 reordanized a bit

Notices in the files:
dev/rat2/rat2b.brd:
(c) 2017 burr settles
